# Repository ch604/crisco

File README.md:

Crisco is a 20% chorded keyboard inspired by the Butterstick, originally created by [Germ](https://github.com/germ) at [gboards.ca](https://www.gboards.ca). The Crisco has a greater saturated fat content and is therefore bigger than it's cousin, being promicro-based instead of SMD, and MX switch spaced. But, it boasts LED strip support, and an OLED 128x32 display.

Butterstick's open source firmware in the qmk repo was used to help create firmware for the Crisco. Thanks also to the [cookpad-pad repo](https://github.com/cookpad/cookpad-pad/tree/master), which jump started the PCB design.

Download [the latest gerber](https://github.com/ch604/crisco/blob/main/gerbers/crisco-v0.3-gerbers.zip?raw=true)

## BOM:
* 1x Arduino Pro Micro (or compatible)
* 20x 1N4148 or 1N4007 through-hole or SMD diodes (or similar)
* 20x 5-pin MX/Choc switches (choc is better for chorded typing because of lower travel)
* 20x MX/Choc keycaps (I recommend even height keycaps like DSA if you choose MX switches)
* 6x 8x2mm rubber feet (or similar, or check out this cool case https://www.thingiverse.com/thing:5538732)
* 1x B3U-1000P reset switch (optional, or similar; I've used a 2x3x4mm switch with mild success)
* capton tape or electrical tape (optional for the next two components)
* 1x 128x32 SSD1306 OLED display (optional)
* 11 LEDs worth of WS2812B 60/m RGB LED strip (optional, or 5 LEDs at 30/m)

## INSTRUCTIONS:

* Solder the diodes D1 through D20 to the top side of the board (on top of the silk screen).
* Solder the legs for the Pro Micro and the Pro Micro itself on the top side of the board, component side up, with the USB port towards the top edge of the board. Check the silk screen for proper pin orientation.
* Solder the switches in place.
* Add some capton tape to the top of the Pro Micro.
* Solder the OLED screen on top of the Pro Micro with the pins to the bottom of the board. Ground will be the square pad.
* Cut and solder the LED strip to the bottom of the board. Ground is the square pad, and "Din" on the strip should go to the middle pin. Keep the strip in place with some more capton tape.
* Apply rubber feet to the bottom of the board to keep it from moving around. If you added the LED strip, you may need some thicker feet.
* Copy the firmware folder contents into your qmk keyboards directory under a new 'crisco' folder. If you used a 30/m strip instead of 60/m, then change config.h to reflect 5 LEDs instead of 11. Regardless of whether you added LEDs or the OLED display, you shouldn't need to turn anything on or off for those  specifically. It will work just fine with or without.
* Compile and flash the firmware.
* Show it off to your discord buddies..
* Get frustrated with the keymap...
* Put it in a drawer for a few months....
* Sell it on /r/mechmarket.....
* Repeat!

## HOW DO I TYPE ON THIS THING?

The default keymap is more or less identical to the [original butterstick keymap](https://qmk.fm/keyboards/butterstick/). The keymap doesn't indicate, but backspace is "vbnm" chorded. I reccomend checking out the keymap file, though its keynames are inherited from steno machines: https://github.com/ch604/crisco/blob/main/firmware/keymaps/default/keymap.c

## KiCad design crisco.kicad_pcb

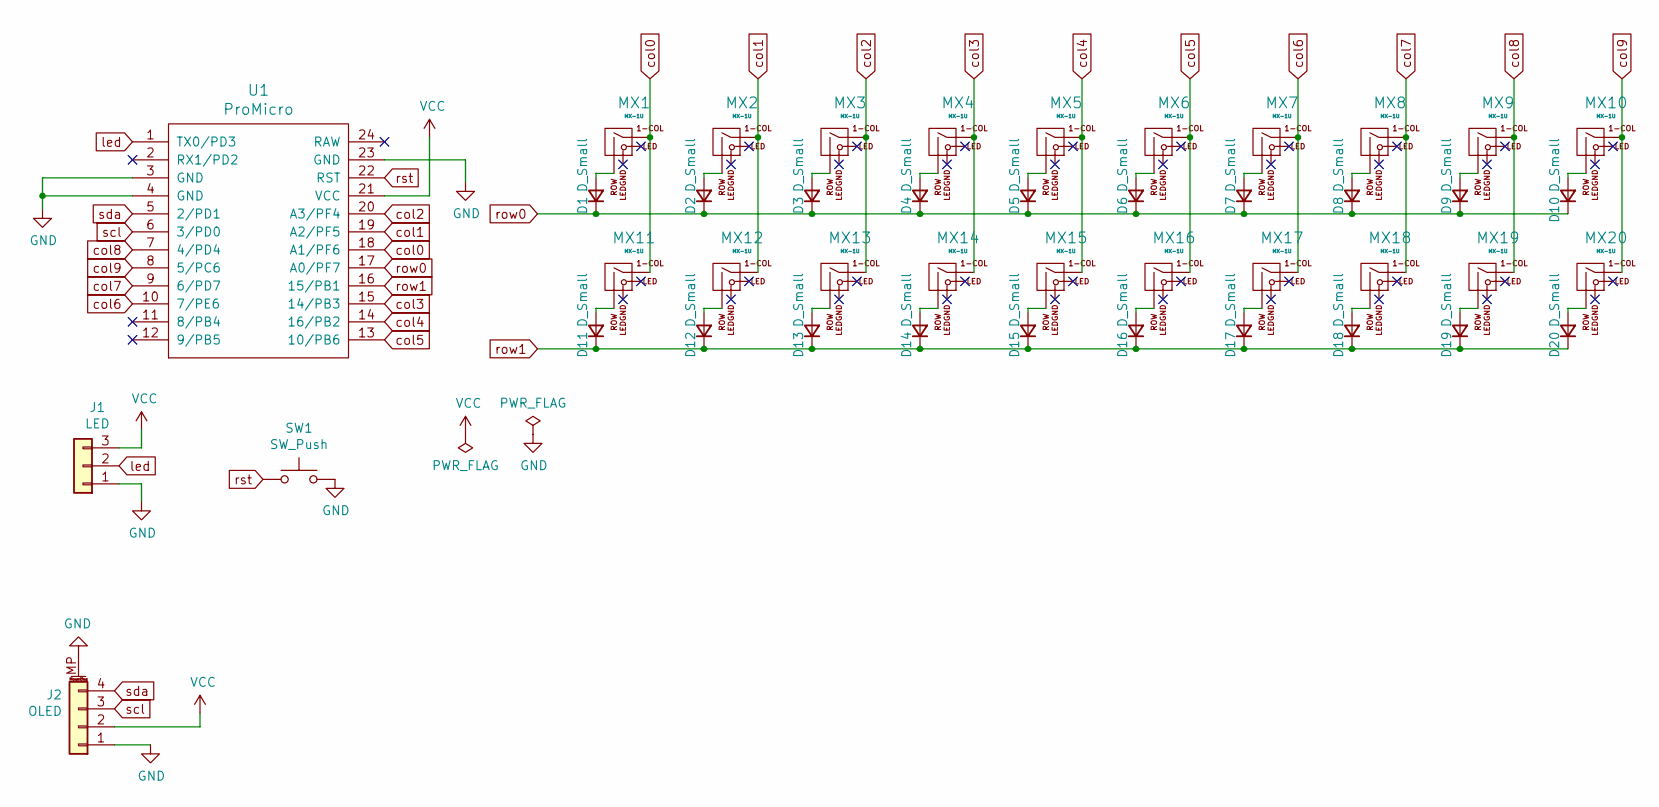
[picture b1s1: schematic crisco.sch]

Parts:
D1, D2, D3, D4, D5, D6, D7, D8, D9, D10, D11, D12, D13, D14, D15, D16, D17, D18, D19, D20: D_Small; D3_TH_SMD
J1: LED; PinHeader_1x03_P2.54mm_Vertical
J2: OLED; PinHeader_1x04_P2.54mm_Vertical
MX1, MX2, MX3, MX4, MX5, MX6, MX7, MX8, MX9, MX10, MX11, MX12, MX13, MX14, MX15, MX16, MX17, MX18, MX19, MX20: MX-1U; MX-Choc-1U-NoLED
SW1: SW_Push; SW_SPST_B3U-1000P
U1: ProMicro; ArduinoProMicro-TopSide

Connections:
GND: J1.1, J2.1, J2.MP (MountPin), SW1.2, U1.3 (GND), U1.4 (GND), U1.23 (GND)
unnamed: D1.2 (A), MX1.2 (ROW)
unnamed: D2.2 (A), MX2.2 (ROW)
unnamed: D3.2 (A), MX3.2 (ROW)
unnamed: D4.2 (A), MX4.2 (ROW)
unnamed: D5.2 (A), MX5.2 (ROW)
unnamed: D6.2 (A), MX6.2 (ROW)
unnamed: D7.2 (A), MX7.2 (ROW)
unnamed: D8.2 (A), MX8.2 (ROW)
unnamed: D9.2 (A), MX9.2 (ROW)
unnamed: D10.2 (A), MX10.2 (ROW)
unnamed: D11.2 (A), MX11.2 (ROW)
unnamed: D12.2 (A), MX12.2 (ROW)
unnamed: D13.2 (A), MX13.2 (ROW)
unnamed: D14.2 (A), MX14.2 (ROW)
unnamed: D15.2 (A), MX15.2 (ROW)
unnamed: D16.2 (A), MX16.2 (ROW)
unnamed: D17.2 (A), MX17.2 (ROW)
unnamed: D18.2 (A), MX18.2 (ROW)
unnamed: D19.2 (A), MX19.2 (ROW)
unnamed: D20.2 (A), MX20.2 (ROW)
VCC: J1.3, J2.2, U1.21 (VCC)
col0: MX1.1 (COL), MX11.1 (COL), U1.18 (A1/PF6)
col1: MX2.1 (COL), MX12.1 (COL), U1.19 (A2/PF5)
col2: MX3.1 (COL), MX13.1 (COL), U1.20 (A3/PF4)
col3: MX4.1 (COL), MX14.1 (COL), U1.15 (14/PB3)
col4: MX5.1 (COL), MX15.1 (COL), U1.14 (16/PB2)
col5: MX6.1 (COL), MX16.1 (COL), U1.13 (10/PB6)
col6: MX7.1 (COL), MX17.1 (COL), U1.10 (7/PE6)
col7: MX8.1 (COL), MX18.1 (COL), U1.9 (6/PD7)
col8: MX9.1 (COL), MX19.1 (COL), U1.7 (4/PD4)
col9: MX10.1 (COL), MX20.1 (COL), U1.8 (5/PC6)
led: J1.2, U1.1 (TX0/PD3)
row0: D1.1 (K), D2.1 (K), D3.1 (K), D4.1 (K), D5.1 (K), D6.1 (K), D7.1 (K), D8.1 (K), D9.1 (K), D10.1 (K), U1.17 (A0/PF7)
row1: D11.1 (K), D12.1 (K), D13.1 (K), D14.1 (K), D15.1 (K), D16.1 (K), D17.1 (K), D18.1 (K), D19.1 (K), D20.1 (K), U1.16 (15/PB1)
rst: SW1.1, U1.22 (RST)
scl: J2.3, U1.6 (3/PD0)
sda: J2.4, U1.5 (2/PD1)

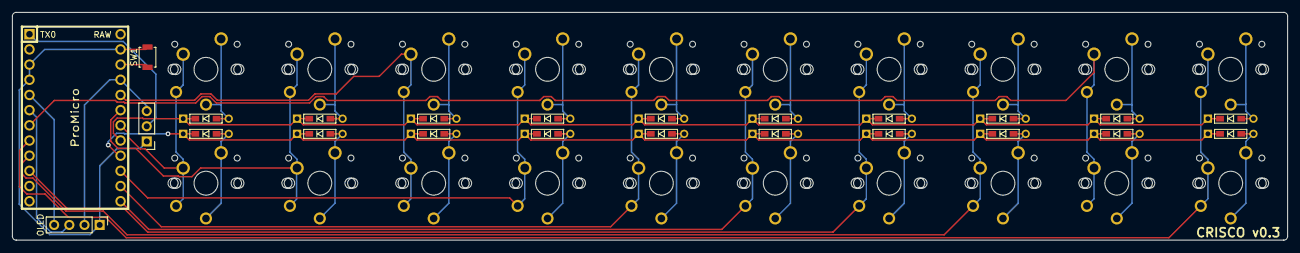
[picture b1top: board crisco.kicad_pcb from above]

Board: 2 copper layers, 213.4 x 38.1 mm, 44 parts (0 on the bottom side), 38 nets.

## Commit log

2021-12-28 readme
2021-12-28 thanks
2021-12-28 initial repo
2021-12-28 gerbers
2021-12-28 gitignore
2021-12-28 gerber link
2021-12-29 bus routing'
2021-12-30 start of firmware
2022-01-03 added pullup resistors, bom, and instructions
2022-01-04 functioning firmware
2022-01-04 config.h
2022-01-04 reorder buttons
2022-01-04 update gerber
2022-01-04 silkscreen update
2022-01-04 reset switch
2022-01-04 update vias
2022-01-04 diode pad flip
2022-01-04 image
2022-01-05 mx/alps hybrid version
2022-01-05 update image
2022-01-05 mv images
2022-01-05 silkscreen
2022-01-05 choc hybrid
2022-01-05 update v3 image
2022-01-05 extra drill for choc
2022-01-30 add assembled image
2023-01-29 Update config.h
    Line 8 and 9 need to be strings or it won't compile
2023-01-29 Update keymap.c
    Changes to make it compile.
